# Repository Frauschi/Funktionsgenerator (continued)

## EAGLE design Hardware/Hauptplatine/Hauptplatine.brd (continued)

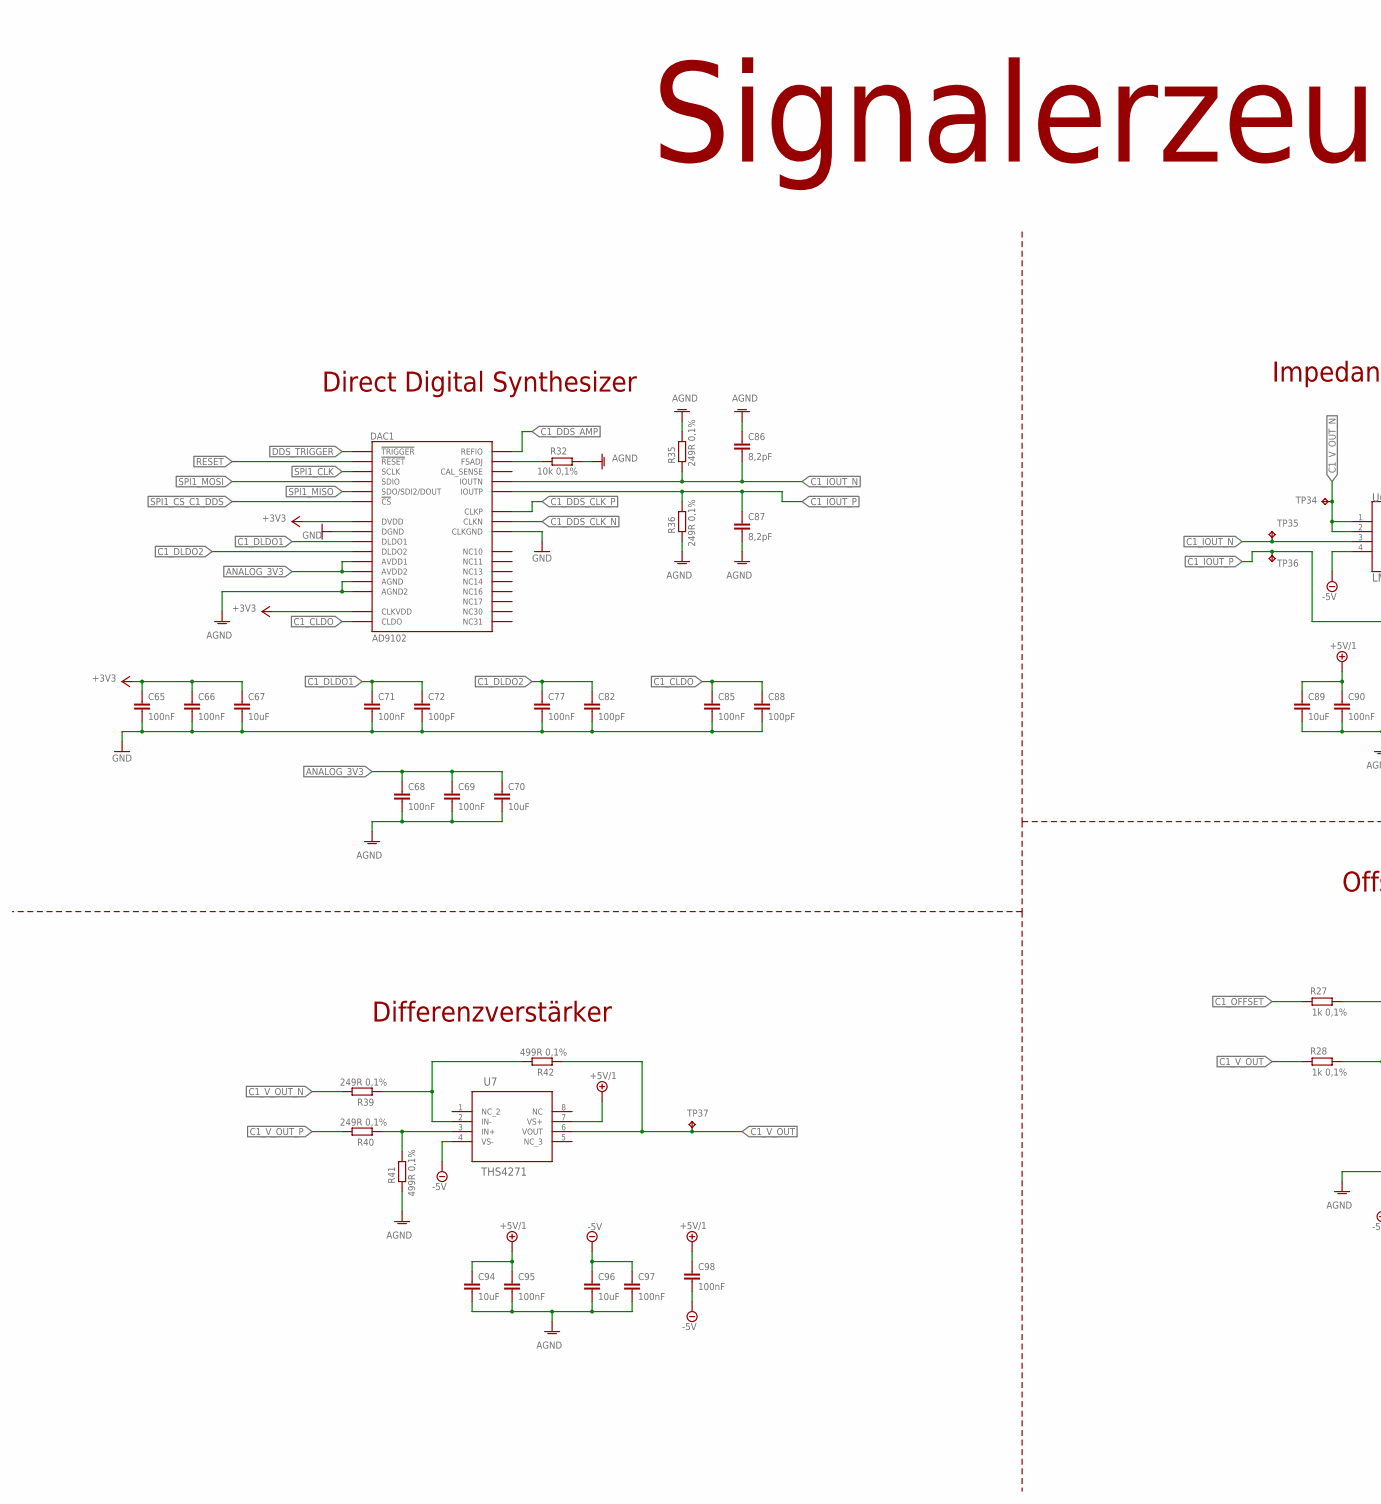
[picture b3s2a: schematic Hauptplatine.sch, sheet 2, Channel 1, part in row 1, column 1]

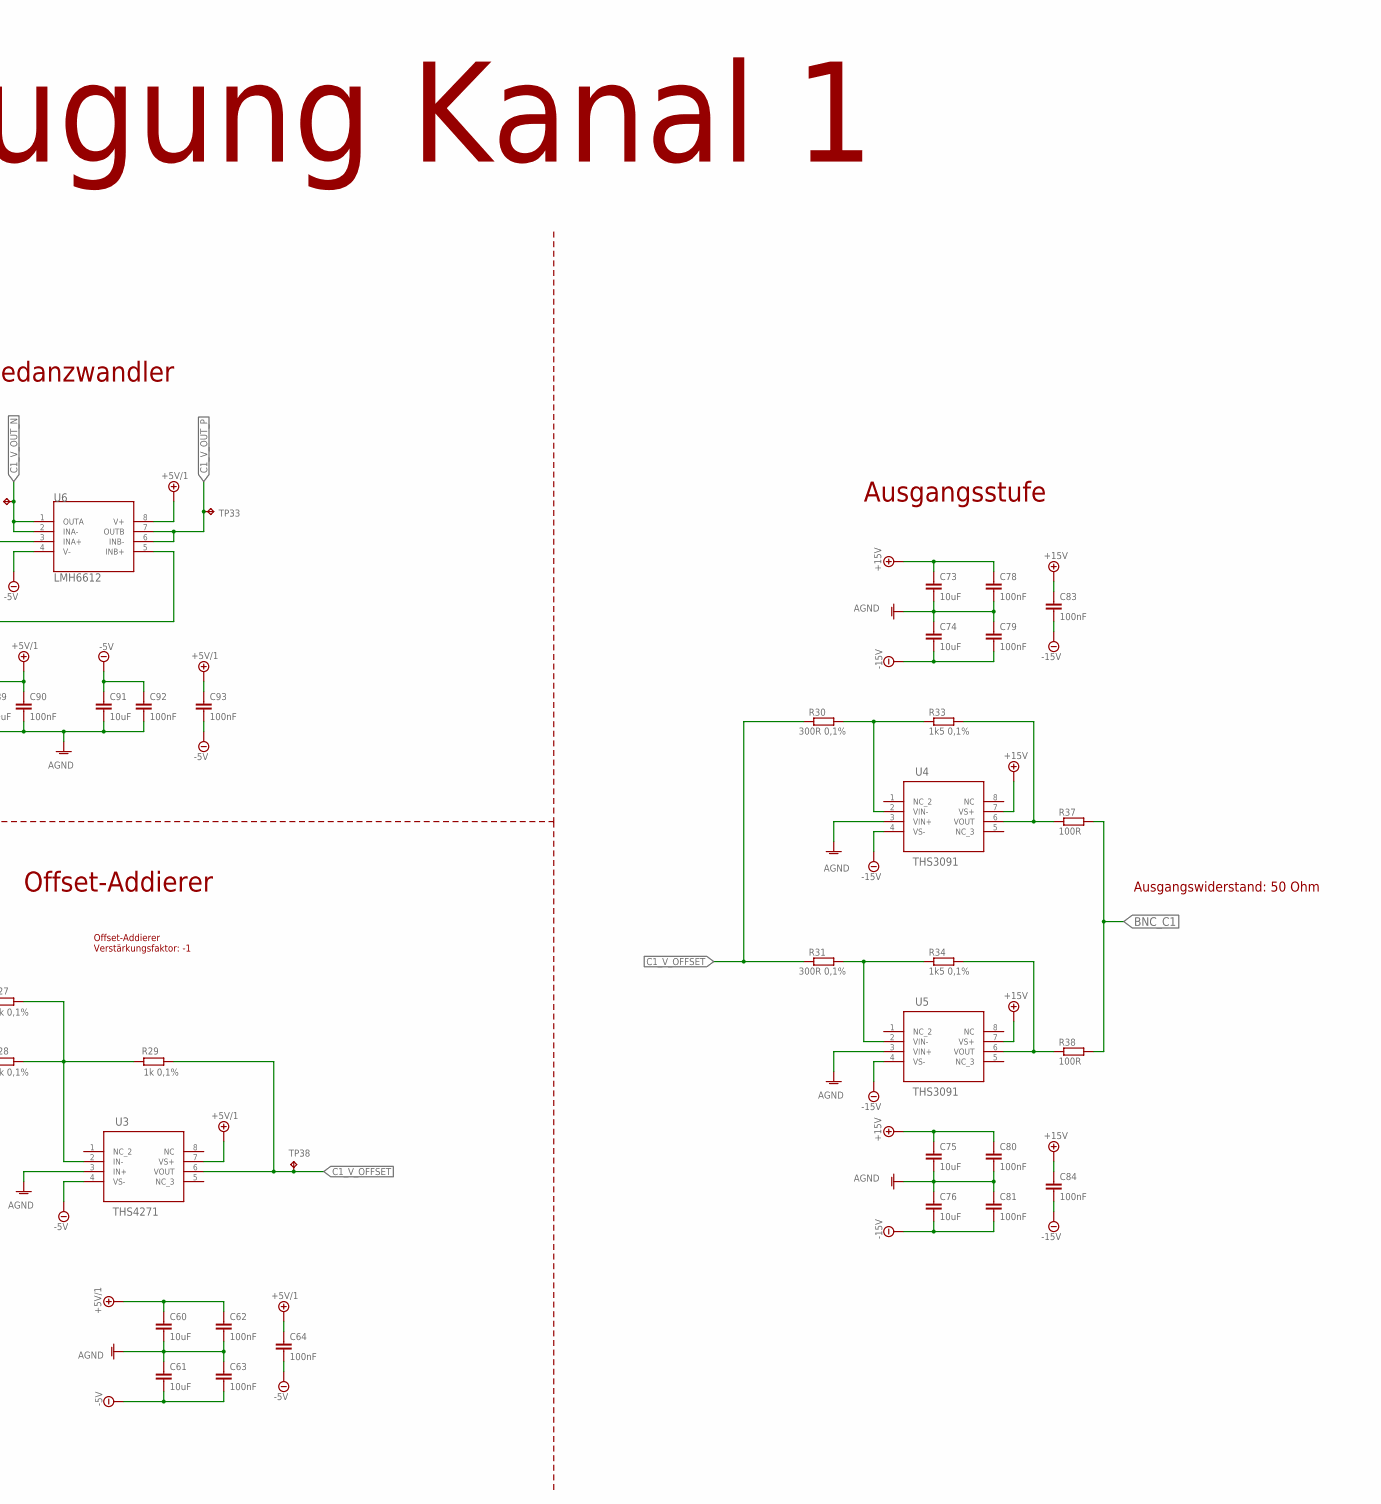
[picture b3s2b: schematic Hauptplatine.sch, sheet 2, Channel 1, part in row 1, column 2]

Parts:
C60, C61, C67, C70, C73, C74, C75, C76, C89, C91, C94, C96: 10uF; C0603
C62, C63, C64, C65, C66, C68, C69, C71, C77, C78, C79, C80, C81, C83, C84, C85, C90, C92, C93, C95, C97, C98: 100nF; C0603
C72, C82, C88: 100pF; C0603
C86, C87: 8,2pF; C0603
DAC1: AD9102; CP_32_12
R27, R28, R29: 1k 0,1%; R0603
R30, R31: 300R 0,1%; R0603
R32: 10k 0,1%; R0603
R33, R34: 1k5 0,1%; R0603
R35, R36, R39, R40: 249R 0,1%; R0603
R37, R38: 100R; R0603
R41, R42: 499R 0,1%; R0603
TP33, TP34, TP35, TP36, TP37, TP38: TPB1,27; B1,27
U3, U7: THS4271; D8-M
U4, U5: THS3091; D8-M
U6: LMH6612; M08A-M

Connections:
+3V3: C65.1, C66.1, C67.1, DAC1.5 (DVDD), DAC1.23 (CLKVDD); also elsewhere on the board
+5V/1: C60.1, C62.1, C64.1, C89.1, C90.1, C93.1, C94.1, C95.1, C98.1, U3.7 (VS+), U6.8 (V+), U7.7 (VS+); also elsewhere on the board
+18V: C73.1, C75.1, C78.1, C80.1, C83.1, C84.1, U4.7 (VS+), U5.7 (VS+); also elsewhere on the board
-5V: C61.2, C63.2, C64.2, C91.1, C92.1, C93.2, C96.1, C97.1, C98.2, U3.4 (VS-), U6.4 (V-), U7.4 (VS-); also elsewhere on the board
-18V: C74.2, C76.2, C79.2, C81.2, C83.2, C84.2, U4.4 (VS-), U5.4 (VS-); also elsewhere on the board
ANALOG_3V3: C68.1, C69.1, C70.1, DAC1.12 (AVDD2), DAC1.29 (AVDD1); also elsewhere on the board
BNC_C1: R37.2, R38.2; also elsewhere on the board
C1_CLDO: C85.1, C88.1, DAC1.22 (CLDO)
C1_DDS_AMP: DAC1.18 (REFIO); also elsewhere on the board
C1_DDS_CLK_N: DAC1.20 (CLKN); also elsewhere on the board
C1_DDS_CLK_P: DAC1.21 (CLKP); also elsewhere on the board
C1_DLDO1: C71.1, C72.1, DAC1.6 (DLDO1)
C1_DLDO2: C77.1, C82.1, DAC1.4 (DLDO2)
C1_IOUT_N: C86.2, DAC1.28 (IOUTN), R35.1, TP35.TP, U6.3 (INA+)
C1_IOUT_P: C87.1, DAC1.27 (IOUTP), R36.2, TP36.TP, U6.5 (INB+)
C1_OFFSET: R27.2; also elsewhere on the board
C1_V_OFFSET: R29.1, R30.1, R31.1, TP38.TP, U3.6 (VOUT)
C1_V_OUT: R28.2, R42.1, TP37.TP, U7.6 (VOUT)
C1_V_OUT_N: R39.2, TP34.TP, U6.1 (OUTA), U6.2 (INA-)
C1_V_OUT_P: R40.2, TP33.TP, U6.6 (INB-), U6.7 (OUTB)
DDS_TRIGGER: DAC1.32 (!TRIGGER); also elsewhere on the board
GND: C60.2, C61.1, C62.2, C63.1, C65.2, C66.2, C67.2, C68.2, C69.2, C70.2, C71.2, C72.2, C73.2, C74.1, C75.2, C76.1, C77.2, C78.2, C79.1, C80.2, C81.1, C82.2, C85.2, C86.1, C87.2, C88.2, C89.2, C90.2, C91.2, C92.2, C94.2, C95.2, C96.2, C97.2, DAC1.3 (DGND), DAC1.15 (AGND), DAC1.19 (CLKGND), DAC1.26 (AGND2), DAC1.33 (DGND), R32.2, R35.2, R36.1, R41.1, U3.3 (IN+), U4.3 (VIN+), U5.3 (VIN+); also elsewhere on the board
unnamed: DAC1.25 (FSADJ), R32.1
unnamed: R40.1, R41.2, U7.3 (IN+)
unnamed: R39.1, R42.2, U7.2 (IN-)
unnamed: R33.2, R37.1, U4.6 (VOUT)
unnamed: R31.2, R34.1, U5.2 (VIN-)
unnamed: R34.2, R38.1, U5.6 (VOUT)
unnamed: R30.2, R33.1, U4.2 (VIN-)
unnamed: R27.1, R28.1, R29.2, U3.2 (IN-)
RESET: DAC1.9 (!RESET); also elsewhere on the board
SPI1_CLK: DAC1.1 (SCLK); also elsewhere on the board
SPI1_CS_C1_DDS: DAC1.8 (!CS); also elsewhere on the board
SPI1_MISO: DAC1.7 (SDO/SDI2/DOUT); also elsewhere on the board
SPI1_MOSI: DAC1.2 (SDIO); also elsewhere on the board

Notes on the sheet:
Signalerzeugung Kanal 1
Direct Digital Synthesizer
Differenzverstärker
Offset-Addierer
Ausgangsstufe
Offset-Addierer Verstärkungsfaktor: -1
Impedanzwandler
Ausgangswiderstand: 50 Ohm

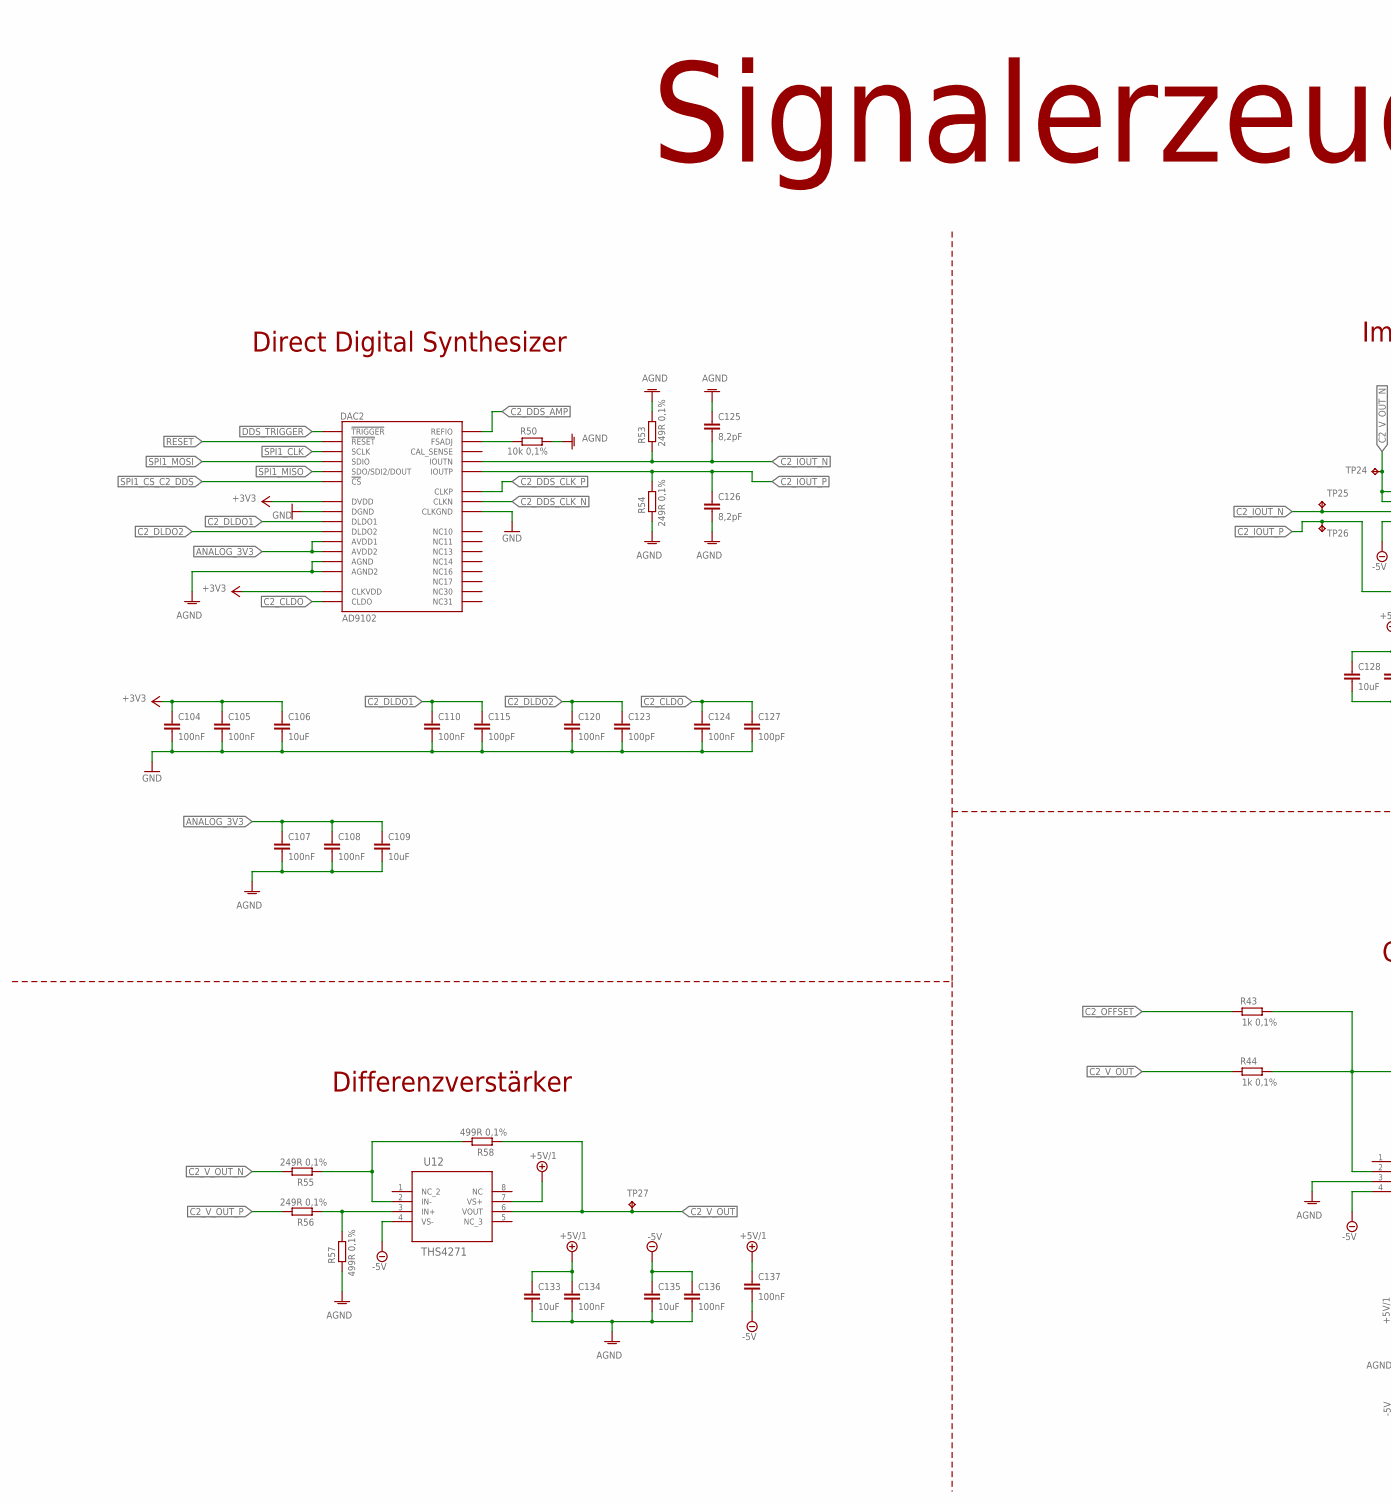
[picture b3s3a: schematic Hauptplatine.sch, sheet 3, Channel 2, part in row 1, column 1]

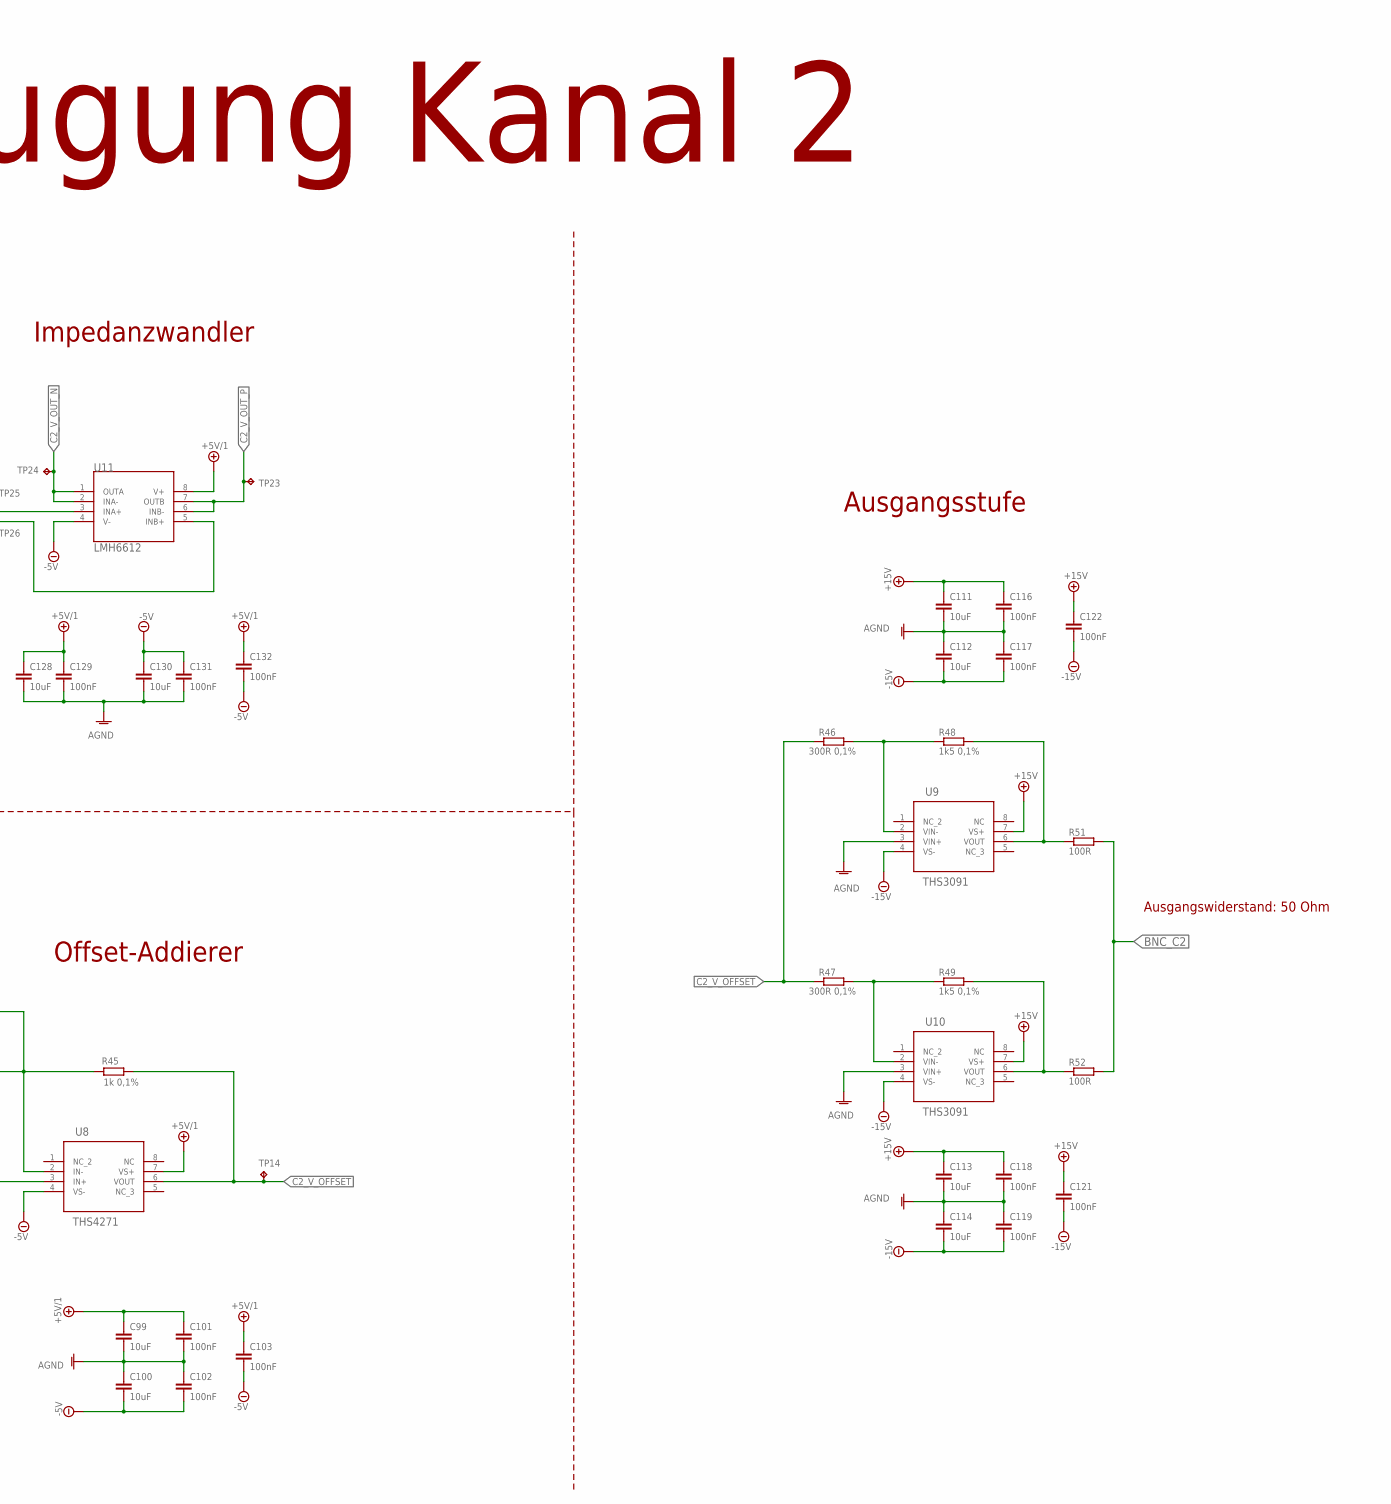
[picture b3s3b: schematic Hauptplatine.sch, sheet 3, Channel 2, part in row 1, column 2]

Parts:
C99, C100, C106, C109, C111, C112, C113, C114, C128, C130, C133, C135: 10uF; C0603
C101, C102, C103, C104, C105, C107, C108, C110, C116, C117, C118, C119, C120, C121, C122, C124, C129, C131, C132, C134, C136, C137: 100nF; C0603
C115, C123, C127: 100pF; C0603
C125, C126: 8,2pF; C0603
DAC2: AD9102; CP_32_12
R43, R44, R45: 1k 0,1%; R0603
R46, R47: 300R 0,1%; R0603
R48, R49: 1k5 0,1%; R0603
R50: 10k 0,1%; R0603
R51, R52: 100R; R0603
R53, R54, R55, R56: 249R 0,1%; R0603
R57, R58: 499R 0,1%; R0603
TP14, TP23, TP24, TP25, TP26, TP27: TPB1,27; B1,27
U8, U12: THS4271; D8-M
U9, U10: THS3091; D8-M
U11: LMH6612; M08A-M

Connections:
+3V3: C104.1, C105.1, C106.1, DAC2.5 (DVDD), DAC2.23 (CLKVDD); also elsewhere on the board
+5V/1: C99.1, C101.1, C103.1, C128.1, C129.1, C132.1, C133.1, C134.1, C137.1, U8.7 (VS+), U11.8 (V+), U12.7 (VS+); also elsewhere on the board
+18V: C111.1, C113.1, C116.1, C118.1, C121.1, C122.1, U9.7 (VS+), U10.7 (VS+); also elsewhere on the board
-5V: C100.2, C102.2, C103.2, C130.1, C131.1, C132.2, C135.1, C136.1, C137.2, U8.4 (VS-), U11.4 (V-), U12.4 (VS-); also elsewhere on the board
-18V: C112.2, C114.2, C117.2, C119.2, C121.2, C122.2, U9.4 (VS-), U10.4 (VS-); also elsewhere on the board
ANALOG_3V3: C107.1, C108.1, C109.1, DAC2.12 (AVDD2), DAC2.29 (AVDD1); also elsewhere on the board
BNC_C2: R51.2, R52.2; also elsewhere on the board
C2_CLDO: C124.1, C127.1, DAC2.22 (CLDO)
C2_DDS_AMP: DAC2.18 (REFIO); also elsewhere on the board
C2_DDS_CLK_N: DAC2.20 (CLKN); also elsewhere on the board
C2_DDS_CLK_P: DAC2.21 (CLKP); also elsewhere on the board
C2_DLDO1: C110.1, C115.1, DAC2.6 (DLDO1)
C2_DLDO2: C120.1, C123.1, DAC2.4 (DLDO2)
C2_IOUT_N: C125.2, DAC2.28 (IOUTN), R53.1, TP25.TP, U11.3 (INA+)
C2_IOUT_P: C126.1, DAC2.27 (IOUTP), R54.2, TP26.TP, U11.5 (INB+)
C2_OFFSET: R43.2; also elsewhere on the board
C2_V_OFFSET: R45.1, R46.1, R47.1, TP14.TP, U8.6 (VOUT)
C2_V_OUT: R44.2, R58.1, TP27.TP, U12.6 (VOUT)
C2_V_OUT_N: R55.2, TP24.TP, U11.1 (OUTA), U11.2 (INA-)
C2_V_OUT_P: R56.2, TP23.TP, U11.6 (INB-), U11.7 (OUTB)
DDS_TRIGGER: DAC2.32 (!TRIGGER); also elsewhere on the board
GND: C99.2, C100.1, C101.2, C102.1, C104.2, C105.2, C106.2, C107.2, C108.2, C109.2, C110.2, C111.2, C112.1, C113.2, C114.1, C115.2, C116.2, C117.1, C118.2, C119.1, C120.2, C123.2, C124.2, C125.1, C126.2, C127.2, C128.2, C129.2, C130.2, C131.2, C133.2, C134.2, C135.2, C136.2, DAC2.3 (DGND), DAC2.15 (AGND), DAC2.19 (CLKGND), DAC2.26 (AGND2), DAC2.33 (DGND), R50.2, R53.2, R54.1, R57.1, U8.3 (IN+), U9.3 (VIN+), U10.3 (VIN+); also elsewhere on the board
unnamed: DAC2.25 (FSADJ), R50.1
unnamed: R56.1, R57.2, U12.3 (IN+)
unnamed: R55.1, R58.2, U12.2 (IN-)
unnamed: R48.2, R51.1, U9.6 (VOUT)
unnamed: R47.2, R49.1, U10.2 (VIN-)
unnamed: R49.2, R52.1, U10.6 (VOUT)
unnamed: R46.2, R48.1, U9.2 (VIN-)
unnamed: R43.1, R44.1, R45.2, U8.2 (IN-)
RESET: DAC2.9 (!RESET); also elsewhere on the board
SPI1_CLK: DAC2.1 (SCLK); also elsewhere on the board
SPI1_CS_C2_DDS: DAC2.8 (!CS); also elsewhere on the board
SPI1_MISO: DAC2.7 (SDO/SDI2/DOUT); also elsewhere on the board
SPI1_MOSI: DAC2.2 (SDIO); also elsewhere on the board

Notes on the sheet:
Signalerzeugung Kanal 2
Direct Digital Synthesizer
Differenzverstärker
Ausgangsstufe
Offset-Addierer
Impedanzwandler
Ausgangswiderstand: 50 Ohm

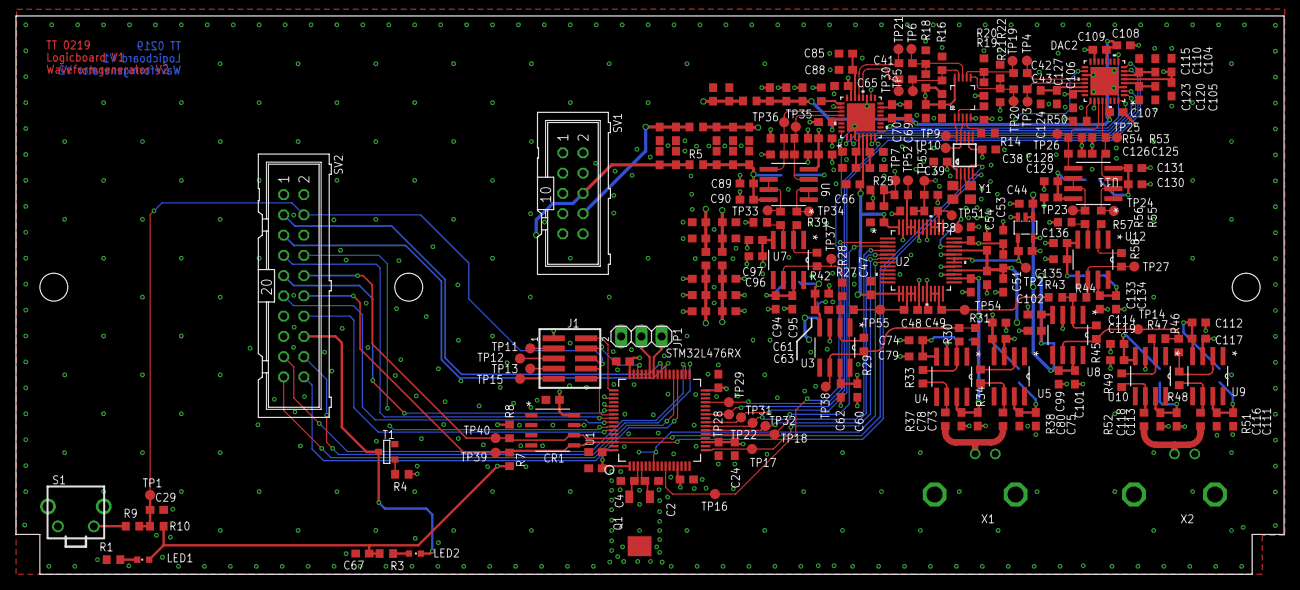
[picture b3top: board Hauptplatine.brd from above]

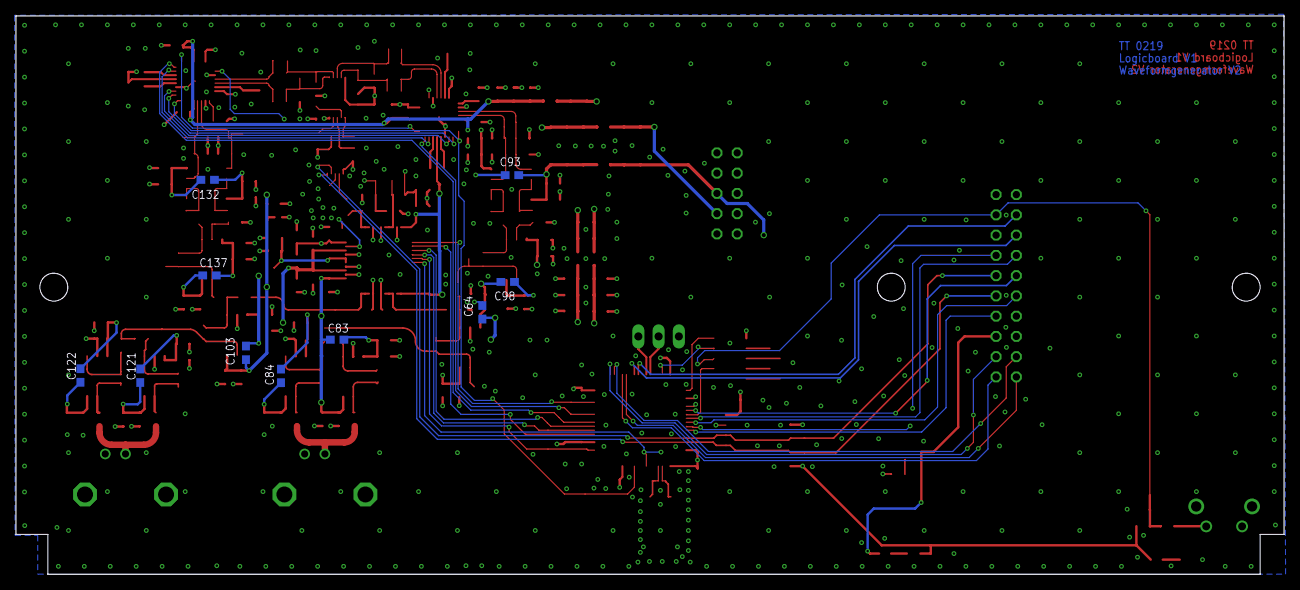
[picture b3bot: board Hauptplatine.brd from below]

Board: 4 copper layers, 159.0 x 70.0 mm, 270 parts (10 on the bottom side), 109 nets.

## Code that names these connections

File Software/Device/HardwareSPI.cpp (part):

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	if(spiBase_ == SPI1) {
		/* SPI1:
		 * 		GPIO	(PA4		SPI1_NSS)
		 * 				PA5			SPI1_SCK
		 * 				PA6			SPI1_MISO
		 * 				PA7			SPI1_MOSI
		 *
		 * 		DMA 1	Channel 2 	SPI1_RX
		 * 				Channel 3	SPI1_TX
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	else if(spiBase_ == SPI2) {
		/* SPI2:
		 *
		 * 		GPIO	(PB12		SPI2_NSS)
		 * 				PB13		SPI2_SCK
		 * 				PB14		SPI2_MISO
		 * 				PB15		SPI2_MOSI
		 *
		 * 		DMA 1	Channel 4	SPI2_RX
		 * 				Channel 5	SPI2_TX
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
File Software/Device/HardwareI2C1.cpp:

#include <HardwareI2C1.h>
#include <cstdint>
#include <functional>
#include "stm32l476xx.h"
#include "HardwareCore.h"


//---------------------------------------------------------------------------------------
// -------------------- Implementation of Class 'HardwareI2C1' --------------------------

Device::HardwareI2C1::
HardwareI2C1()
{
	using namespace Device;
	/* 	I2C1:
	 * 		GPIO	PB8			I2C1_SCL
	 * 				PB9			I2C1_SDA
	 *
	 *		DMA 1 	Channel 6	I2C1_Tx
	 *				Channel 7	I2C1_Rx
	 */

	/* Enable clocks for GPIOB, DMA1 and I2C1 */
	RCC->AHB2ENR	|= 0x01<<1;		/* GPIOB enable */
	RCC->AHB1ENR	|= 0x01<<0; 	/* DMA1 enable */
	RCC->APB1ENR1	|= 0x01<<21; 	/* I2C1 enable */

	/* Configure GPIOB Pin 8 (SCL) and 9 (SDA) */
	GPIOB->AFR[1]	 =  (GPIOB->AFR[1] & ~(0xFF)) | (0x04<<0 | 0x04<<4);
	GPIOB->MODER	 = (GPIOB->MODER & ~(0x0F<<16)) | (0x02<<16 | 0x02<<18);
	GPIOB->OTYPER	|= (0x01<<8 | 0x01<<9);
	GPIOB->OSPEEDR	|= (0x03<<16 | 0x03<<18);
	GPIOB->PUPDR	&= ~(0x03<<16 | 0x03<<18);	/* Disable internal pull ups */

	/* Configure DMA1 channel 6 (Tx) */
	/* Medium prio, 8 bit memory / peripheral size, memory increment mode, read from memory, Channel disabled
	 */
	DMA1_Channel6->CCR	|= (0x01<<12 | 0x01<<7 | 0x01<<4);
	DMA1_Channel6->CPAR	 = reinterpret_cast<std::uint32_t>(&I2C1->TXDR);	/* I2C1 Tx data register is destination address */

	/* Configure DMA1 channel 7 (Rx) */
	/* Medium prio, 8 bit memory / peripheral size, memory increment mode, read from peripheral, Channel disabled
	 */
	DMA1_Channel7->CCR	|= (0x01<<12 | 0x01<<7);
	DMA1_Channel7->CPAR	 = reinterpret_cast<std::uint32_t>(&I2C1->RXDR);	/* I2C1 Rx data register is source address */

	DMA1_CSELR->CSELR	|= (0x03<<20 | 0x03<<24);	/* DMA1 Channel 6 mapped to I2C1_Tx, Channel 7 mapped to I2C1_Rx */

	/* Disable I2C1 */
	I2C1->CR1		&= ~(0x01<<22 | 0x01<<0);

	/* Enable Fast mode plus driving capabilities */
	SYSCFG->CFGR1	|= (0x01<<20 | 0x01<<19 | 0x01<<18);

	/* Set proper timing: Fast-mode (400kHz) */
	enum { PRESC 	= 1 };
	enum { SCLL  	= 9 };
	enum { SCLH  	= 3 };
	enum { SDADEL  	= 1 };
	enum { SCLDEL  	= 3 };

	I2C1->TIMINGR	 = (PRESC<<28 | SCLDEL<<20 | SDADEL<<16 | SCLH<<8 | SCLL<<0);

	/* Enable Own Address register 1 (done in HAL, too) */
	I2C1->OAR1		|= 0x01<<15;

	/* Enable AUTOEND */
	I2C1->CR2		|= 0x01<<25;

	/* NBYTES to send*/
	I2C1->CR2		|= 0x01<<16;

	/* Enable I2C1 */
	I2C1->CR1		|= 0x01<<0;

	/* Configure I2C1 interrupts */
	InterruptMgr::reference().addHandlerForInterrupt(InterruptId::I2C1_EVInt, [this]() { this->i2cEventHandler(); });
	InterruptMgr::reference().addHandlerForInterrupt(InterruptId::I2C1_ERInt, [this]() { this->i2cErrorHandler(); });

	/* Configure DMA interrupts */
	InterruptMgr::reference().addHandlerForInterrupt(InterruptId::DMA1_CH6Int, [this]() { this->dmaTxHandler(); });
	InterruptMgr::reference().addHandlerForInterrupt(InterruptId::DMA1_CH7Int, [this]() { this->dmaRxHandler(); });
 }


Device::HardwareI2C1::
~HardwareI2C1()
{
	// Disable interrupts
	Device::InterruptMgr::reference().disableInterrupt(Device::InterruptId::I2C1_EVInt);
	Device::InterruptMgr::reference().disableInterrupt(Device::InterruptId::I2C1_ERInt);
	Device::InterruptMgr::reference().disableInterrupt(Device::InterruptId::DMA1_CH6Int);
	Device::InterruptMgr::reference().disableInterrupt(Device::InterruptId::DMA1_CH7Int);

	// Disable clock
	RCC->APB1ENR1	&= ~(0x01<<21);
}


void Device::HardwareI2C1::
beginTransmit(const std::uint8_t slaveAddress, const std::uint8_t* dataSrc, const std::size_t numOfBytes) const
{
	/* Configure DMA Tx Channel and enable it */
	DMA1->IFCR			|= 0x01<<20;
	DMA1_Channel6->CNDTR = numOfBytes;
	DMA1_Channel6->CMAR	 = reinterpret_cast<std::uint32_t>(dataSrc);
	DMA1_Channel6->CCR	|= (0x01<<3 | 0x01<<1 | 0x01<<0); /* Transfer error and Transfer complete interrupt enable */


	/* Configure Interrupts and DMA usage */
	I2C1->CR1	|= (0x01<<14 | 0x01<<7 | 0x01<<6 | 0x01<<4);

	/* Configure Transmission parameters and set start bit (Bit 31 is set in the HAL although there is no
	 * mention of it in the datasheet) */
	I2C1->CR2	 = (I2C1->CR2 & ~(0xFF<<16 | 0x01<<10 | 0x3FF<<0)) | ((numOfBytes & 0xFF)<<16 | (slaveAddress&0x7F)<<1 | 0x01<<13);
}


void Device::HardwareI2C1::
beginReceive(const std::uint8_t slaveAddress, const std::uint8_t* dataDest, const std::size_t numOfBytes) const
{
	/* Configure DMA Rx Channel */
	DMA1->IFCR			|= 0x01<<24;
	DMA1_Channel7->CNDTR = numOfBytes;
	DMA1_Channel7->CMAR	 = reinterpret_cast<std::uint32_t>(dataDest);
	DMA1_Channel7->CCR	|= (0x01<<3 | 0x01<<1 | 0x01<<0);

	/* Configure Interrupts and DMA usage */
	I2C1->CR1	|= (0x01<<15 | 0x01<<7 | 0x01<<6 | 0x01<<4);

	/* Configure Reception parameters */
	I2C1->CR2	 = (I2C1->CR2 & ~(0xFF<<16 | 0x01<<10 | 0x3FF<<0)) | ((numOfBytes & 0xFF)<<16 | 0x01<<13 | 0x01<<10 | (slaveAddress&0x7F)<<1);
}


/* Interrupt handler */
void Device::HardwareI2C1::
i2cEventHandler(void) const
{
	/* Called when the transfer is complete  */
	I2C1->ICR	|= I2C1->ISR;
}


void Device::HardwareI2C1::
i2cErrorHandler(void) const
{
	/* Called when an I2C error occured */
	I2C1->ICR	|= I2C1->ISR;

	/* Execute callback handler */
	writeCompleteHandler_(MiscStuff::ErrorCode::Error);
}


void Device::HardwareI2C1::
dmaTxHandler(void) const
{
	/* DMA 1 Channel 6
	 * Called when all bytes to send are transmitted or an error occured */
	/* Check if there is an error or the Transmission is done
	 */
	/* Temporarely store the data in the status register */
	std::uint32_t statusReg = DMA1->ISR;

	/* Clear interrupt source */
	DMA1->IFCR	|= (0x01<<20);

	/* Disable channel and interrupts */
	DMA1_Channel6->CCR	&= ~(0x01<<3 | 0x01<<1 | 0x01<<0);

	/* Disable I2C1 */
	I2C1->CR1	&= ~(0x01<<14 | 0x01<<7 | 0x01<<6 | 0x01<<4);

	/* Check which interrupt occured */
	if (statusReg & 0x01<<23) {
		/* Error */
		writeCompleteHandler_(MiscStuff::ErrorCode::Error);
	}
	else if (statusReg & 0x01<<21) {
		/* Transmission complete */
		writeCompleteHandler_(MiscStuff::ErrorCode::Success);
	}
}


void Device::HardwareI2C1::
dmaRxHandler(void) const
{
	/* DMA 1 Channel 7
	 * Called when all bytes to receive are transmitted or an error occured */
	/* Check if there is an error or the Reception is done
	 */
	/* Temporarely store the data in the status register */
	std::uint32_t statusReg = DMA1->ISR;

	/* Clear interrupt source */
	DMA1->IFCR	|= (0x01<<24);

	/* Disable channel and interrupts */
	DMA1_Channel7->CCR	&= ~(0x01<<3 | 0x01<<1 | 0x01<<0);

	/* Disable I2C1 */
	I2C1->CR1	&= ~(0x01<<15 | 0x01<<7 | 0x01<<6 | 0x01<<4);


	if (statusReg & 0x01<<27) {
		/* Error */
		readCompleteHandler_(MiscStuff::ErrorCode::Error);
	}
	else if (statusReg & 0x01<<25) {
		/* Reception complete */
		readCompleteHandler_(MiscStuff::ErrorCode::Success);
	}
}

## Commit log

2019-04-05 Added Software as a git submodule
2019-04-05 Removed Software submodule
2019-04-05 Removed submodules
2019-04-05 Added Hardware documents
2019-04-05 Added microcontroller firmware in Software folder
2019-04-09 Added images
2019-04-09 Added two images of the complete and finished device
2019-04-12 Updated README for Software
2019-04-12 Added README for Hardware folder
2019-04-12 Removed unnecessary files
2019-04-12 Added files for documentation
2019-04-25 changed Readme
